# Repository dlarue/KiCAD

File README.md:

# KiCAD Projects
* [ProMini LoRaWAN node](ProMini-LoRAWAN-node/)

## License
Projects are licensed under Creative Commons Attribution-ShareAlike 4.0 Unported License (CC BY-SA 4.0)

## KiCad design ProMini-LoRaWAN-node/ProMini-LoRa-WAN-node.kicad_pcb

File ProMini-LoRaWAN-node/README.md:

# ProMini LoRaWAN Node
A LoRaWAN node based on the Arduino ProMini and the RFM95 LoRa module

## Parts
* Arduino Pro Mini 3.3V, 8 Mhz
* RFM95 module (frequency band based on your location)
* Pin headers
* Edge-mounted SMA connector (e.g. [this part](https://www.digikey.com/product-detail/en/rf-solutions/CON-SMA-EDGE-S/CON-SMA-EDGE-S-ND/5845767)) or wire-antenna of correct length

## Additional information
* Board can be powered directly from 2 AA batteries to the 3.3V input
* [Full tutorial using this board by Frank Beks](https://www.thethingsnetwork.org/labs/story/creating-a-ttn-node)

## License
Licensed under Creative Commons Attribution-ShareAlike 4.0 Unported License (CC BY-SA 4.0)

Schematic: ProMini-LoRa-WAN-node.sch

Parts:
P1: Ant_SMA; SMA_EDGE
P2: Power Input; PINHEAD1-3
P3: CONN_1; Pin_Header_Straight_1x06
P4: CONN_2; Pin_Header_Straight_1x02
P5: CONN_3; Pin_Header_Straight_1x04
P6: CONN_4; Pin_Header_Straight_1x04
P7: Ant; PINTST
U1: RFM95HW; RFM69HW_SMD_Handsoldering-Narrow
uP1: ARDUPROMINI-6-2; pro_mini-26

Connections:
+3V3: P2.3, P6.4, U1.13, uP1.21 (Vcc2)
A0: P5.4, uP1.17 (A0)
A1: P5.3, uP1.18 (A1)
A2: P5.2, uP1.19 (A2)
A3: P5.1, uP1.20 (A3)
Ant: P1.1, P7.1, U1.9
CLK: U1.4, uP1.16 (D13)
D2: P3.5, uP1.5 (D2)
D3: P3.6, uP1.6 (D3)
D4: U1.14, uP1.7 (D4)
D5: U1.15, uP1.8 (D5)
D6: U1.7, uP1.9 (D6)
D7: U1.16, uP1.10 (D7)
D8: P4.1, uP1.11 (D8)
D9: P4.2, uP1.12 (D9)
D10: U1.5, uP1.13 (D10)
GND: P1.2, P2.2, P3.4, P6.2, U1.1, U1.8, U1.10, uP1.4 (GND), uP1.23 (GND3)
MISO: U1.2, uP1.15 (D12)
MOSI: U1.3, uP1.14 (D11)
unnamed: P2.1, uP1.24 (RAW)
RESET: P3.3, uP1.3 (RESET)
RX1: P3.2, uP1.2 (RX1)
SCL: P6.3, uP1.26 (A5-SCL)
SDA: P6.1, uP1.25 (A4-SDA)
TX0: P3.1, uP1.1 (TX0)

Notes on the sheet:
VCC 3.3V GND GND D4 4 DIO0 D5 5 DIO1 D6 6 DIO5 D7 7 DIO2 D10-SS 10 NSS MOSI 11 MOSI MISO 12 MISO CLK 13 SCK

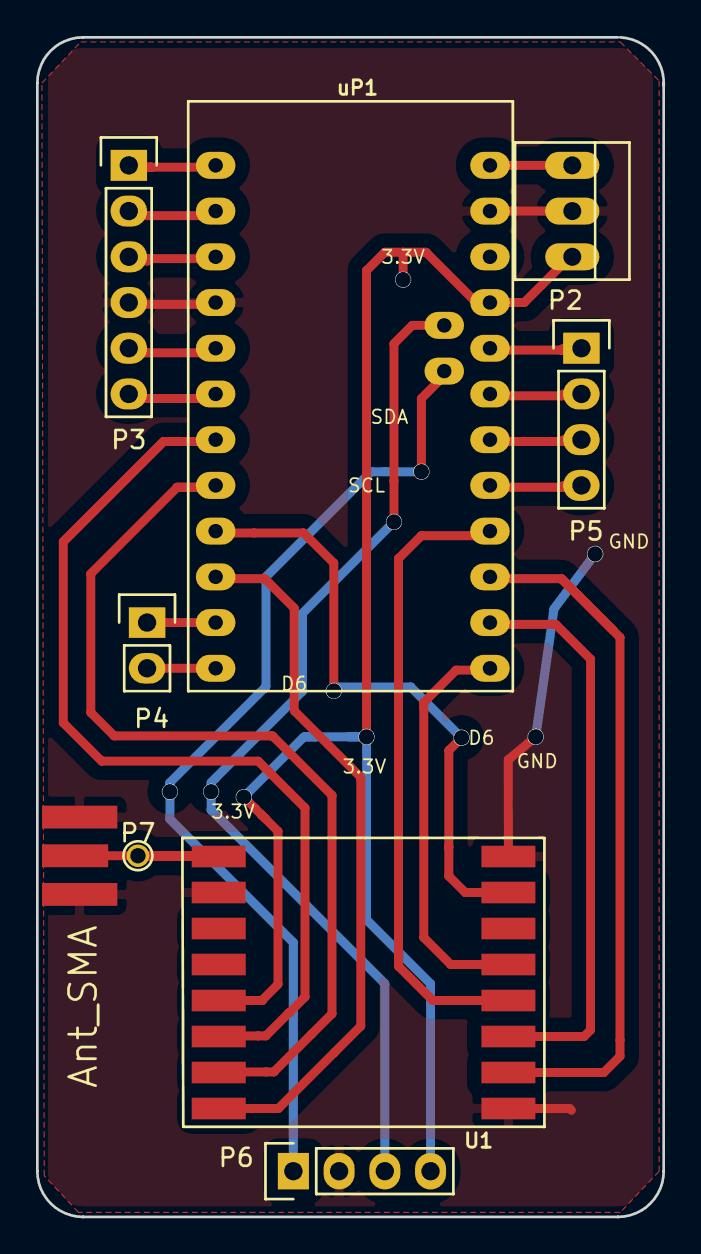
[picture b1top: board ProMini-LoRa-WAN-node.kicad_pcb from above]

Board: 2 copper layers, 34.8 x 65.5 mm, 9 parts (0 on the bottom side), 25 nets.

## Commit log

2017-05-29 initial checkin
2019-10-16 set license as CC-BY-SA
2019-10-16 updated license to CC-BY-SA v4.0
2019-10-22 cleanup, readme
